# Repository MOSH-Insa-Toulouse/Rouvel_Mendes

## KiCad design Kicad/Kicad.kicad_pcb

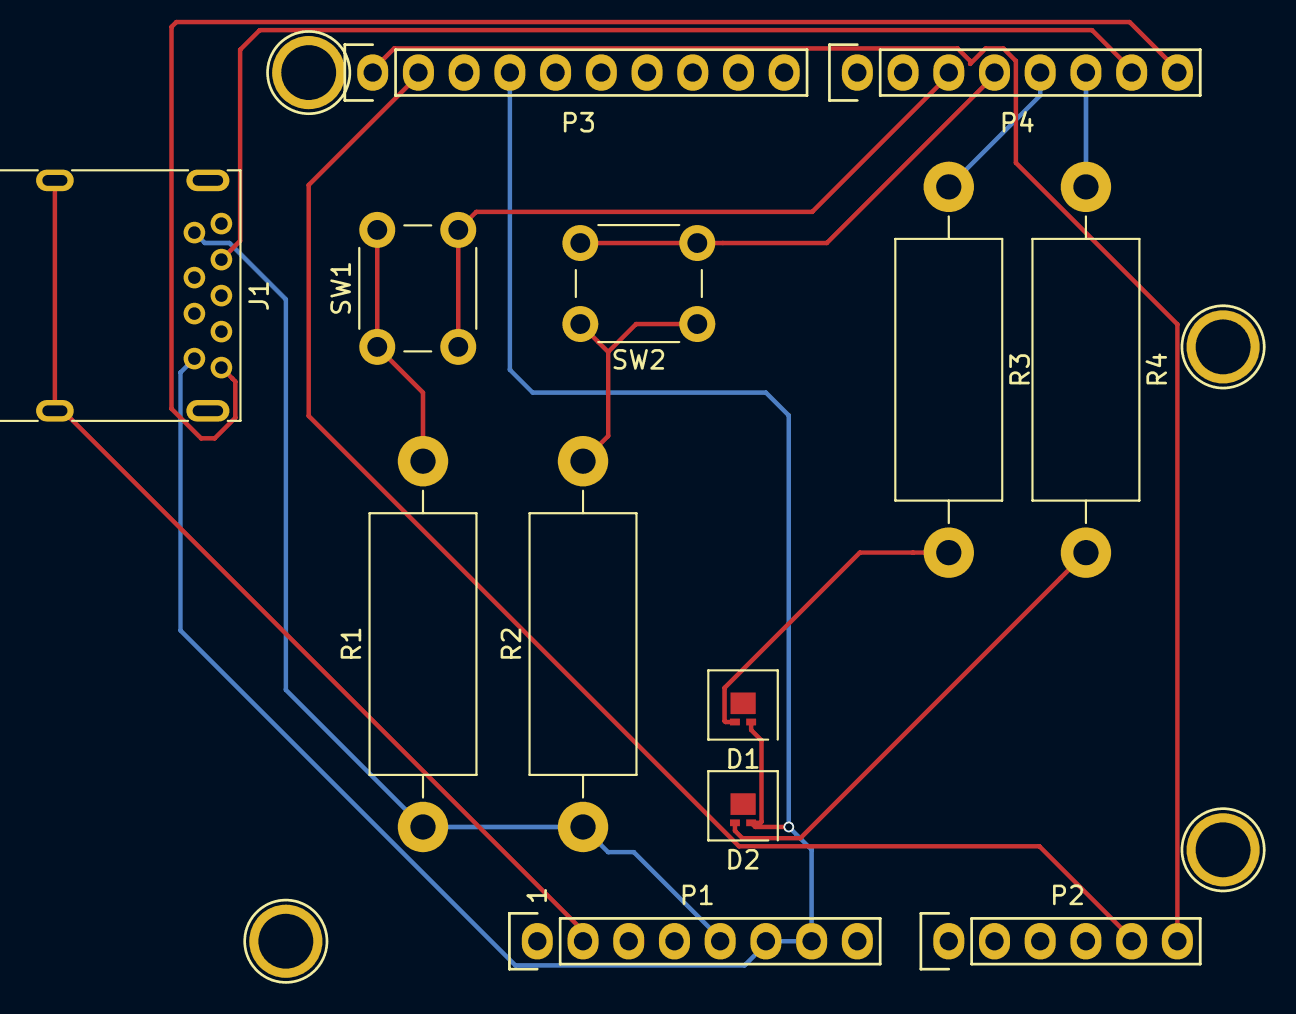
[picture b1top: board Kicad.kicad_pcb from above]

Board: 2 copper layers, 17 parts (0 on the bottom side), 15 nets.

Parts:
D1, D2: LED; LED-L1T2_LUMILEDS
J1: USB3_A; USB3_A_Molex_48393-001
P1: Power; Socket_Strip_Arduino_1x08
P2: Analog; Socket_Strip_Arduino_1x06
P3: Digital; Socket_Strip_Arduino_1x10
P4: Digital; Socket_Strip_Arduino_1x08
P5, P6, P7, P8: CONN_01X01; Arduino_1pin
R1, R2, R3, R4: 100; R_Axial_DIN0614_L14.3mm_D5.7mm_P20.32mm_Horizontal
SW1, SW2: SW_Push; SW_PUSH_6mm_H5mm

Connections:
+5V: J1.1, P1.5, R1.1, R2.1
/0(Rx): J1.5, P4.8
/1(Tx): J1.8, P4.7
/2: P4.6, R4.1
/3(**): P4.5, R3.1
/4: P4.4, SW2.2
/5(**): P4.3, SW1.2
/A4(SDA): P2.5, P3.2
/A5(SCL): P2.6, P3.1
/IOREF: J1.10, P1.2
GND: D1.1, D2.1, J1.4, P1.6, P1.7, P3.4
unnamed: D1.2, R3.2
unnamed: D2.2, R4.2
unnamed: R1.2, SW1.1
unnamed: R2.2, SW2.1
